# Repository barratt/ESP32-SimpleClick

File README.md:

I was looking for a simple small ESP32 that could be used as a desktop or portable IOT button.

The rationale behind not using Zigbee or BLE was simplicity & cost for the end user. It can either be connected via type C to a PC or through WiFi using a battery.

If you're looking to build one, I sent everything in the gerbers folder to JLCPCB and paid for SMD assembly. In total I paid £20 for 5 boards, so £4 per button overall. The button and LED needs soldering by hand, however since they're the biggest components, this is easy.

You can see a full bom in the gerbers folder.

Some issues that need addressing:

- The capacitors on the 3.3v line feeding the ESP are not connected. (I fixed this after using a blob of solder)
- The battery charging module does not output sufficient current with no battery connected - which means the LDO regulator does not get enough power to supply the ESP32.
This can be solved by adding 2 low drop diodes to the schematic, or just removing the battery charging and soldering the LDO input to 5v (like I did in a bodge).
- The RGB LED connector is untested - I didn't need this 
- There are no jumpers / test points to put the ESP into programming mode. As such you'll need to solder leads to the ESP directly and remove them after flashing, as shown in the images below.

It's unlikely I'll come back to the project as it solves my requirements, so if you do fix any of the above please submit a pull request, otherwise do what you like with this!

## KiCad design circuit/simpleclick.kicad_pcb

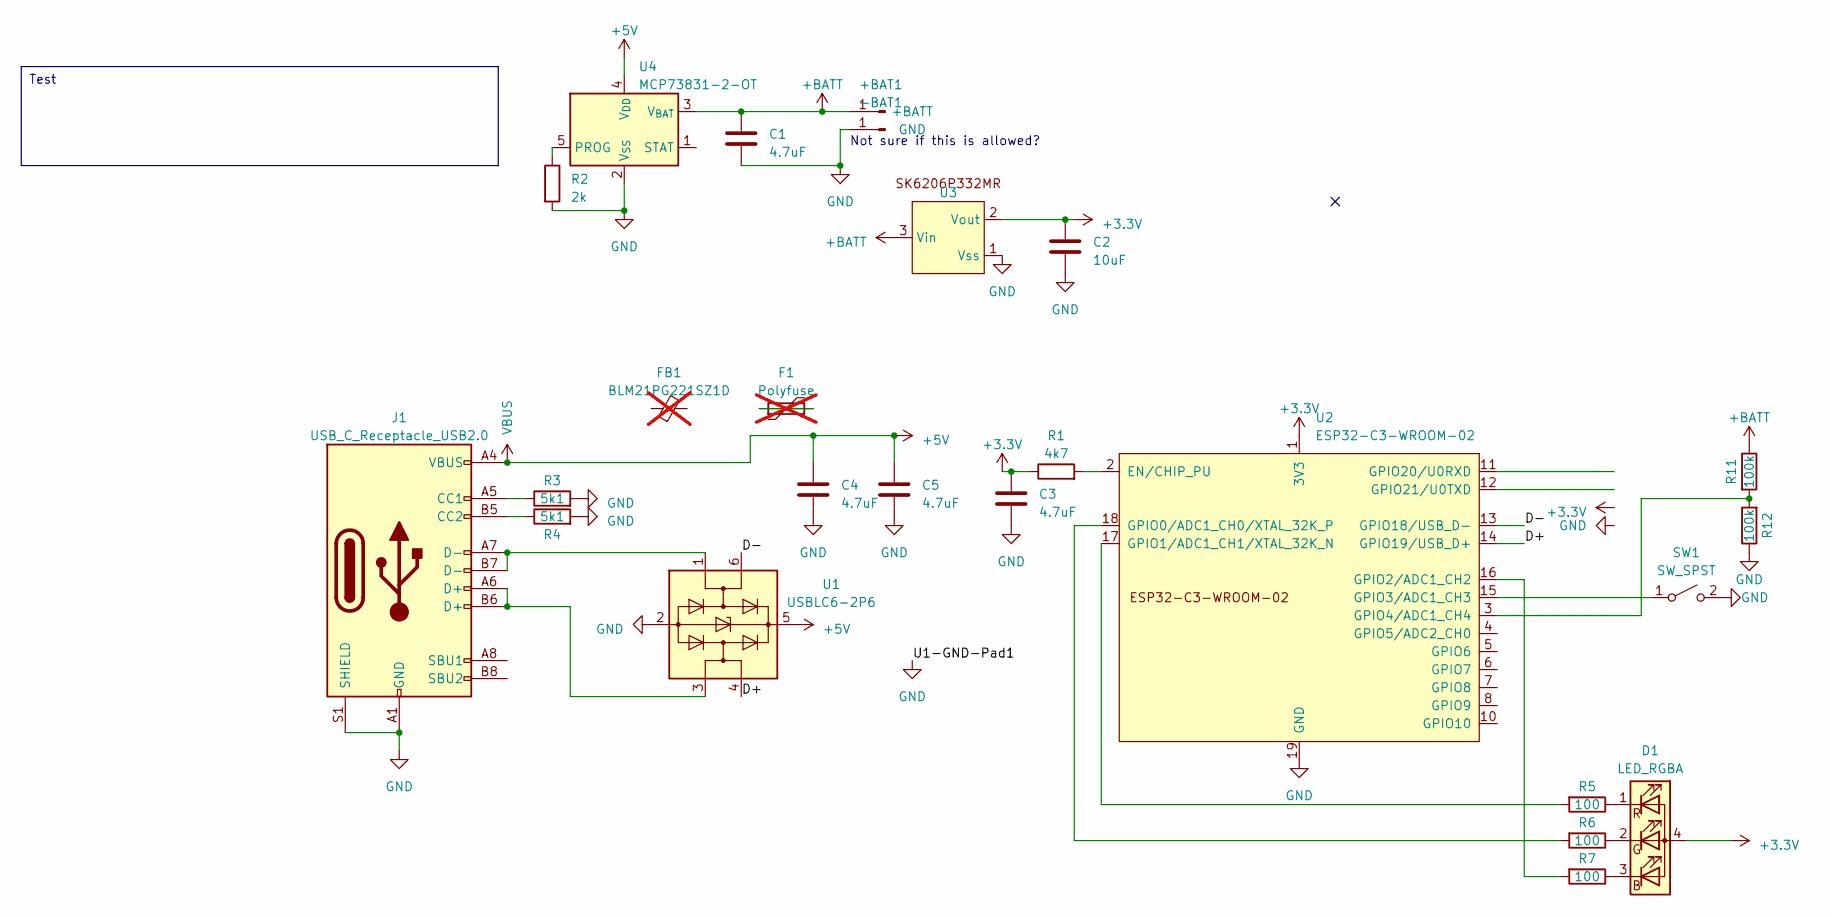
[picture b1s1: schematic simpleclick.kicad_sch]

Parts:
+BAT1: +BATT; TestPoint_Pad_D2.0mm
-BAT1: GND; TestPoint_Pad_D2.0mm
C1, C3, C4, C5: 4.7uF; C_0805_2012Metric_Pad1.18x1.45mm_HandSolder
C2: 10uF; C_0805_2012Metric_Pad1.18x1.45mm_HandSolder
D1: LED_RGBA; LED_D5.0mm-4_RGB
F1: Polyfuse; R_0805_2012Metric_Pad1.20x1.40mm_HandSolder; not fitted
FB1: BLM21PG221SZ1D; R_0805_2012Metric_Pad1.20x1.40mm_HandSolder; not fitted
J1: USB_C_Receptacle_USB2.0; USB_C_Receptacle_G-Switch_GT-USB-7010ASV
R1: 4k7; R_0805_2012Metric_Pad1.20x1.40mm_HandSolder
R2: 2k; R_0805_2012Metric_Pad1.20x1.40mm_HandSolder
R3, R4: 5k1; R_0805_2012Metric_Pad1.20x1.40mm_HandSolder
R5, R6, R7: 100; R_0603_1608Metric_Pad0.98x0.95mm_HandSolder
R11, R12: 100k; R_0805_2012Metric_Pad1.20x1.40mm_HandSolder
SW1: SW_SPST; tact12x12
U1: USBLC6-2P6; SOT-666
U2: ESP32-C3-WROOM-02
U3: SC-59_Handsoldering
U4: MCP73831-2-OT; SOT-23-5

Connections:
+3.3V: C2.1, C3.1, D1.4 (A), R1.1, U2.1 (3V3), U3.2 (Vout)
+5V: C4.1, C5.1, J1.A4 (VBUS), J1.A9 (VBUS), J1.B4 (VBUS), J1.B9 (VBUS), U1.5 (VBUS), U4.4 (V_{DD})
+BATT: +BAT1.1, C1.1, R11.1, U3.3 (Vin), U4.3 (V_{BAT})
/D+: U1.4 (I/O2), U2.14 (GPIO19/USB_D+)
/D-: U1.6 (I/O1), U2.13 (GPIO18/USB_D-)
GND: -BAT1.1, C1.2, C2.2, C3.2, C4.2, C5.2, J1.A1 (GND), J1.A12 (GND), J1.B1 (GND), J1.B12 (GND), J1.S1 (SHIELD), R2.2, R3.2, R4.2, R12.1, SW1.2 (B), U1.2 (GND), U2.9 (GND), U2.19 (GND), U3.1 (Vss), U4.2 (V_{SS})
unnamed: D1.3 (BK), R7.1
unnamed: D1.2 (GK), R6.1
unnamed: D1.1 (RK), R5.1
unnamed: F1.1, F1.2
unnamed: J1.A5 (CC1), R3.1
unnamed: J1.B5 (CC2), R4.1
unnamed: J1.A6 (D+), J1.B6 (D+), U1.3 (I/O2)
unnamed: J1.A7 (D-), J1.B7 (D-), U1.1 (I/O1)
unnamed: SW1.1 (A), U2.15 (GPIO3/ADC1_CH3)
unnamed: R1.2, U2.2 (EN/CHIP_PU)
unnamed: R6.2, U2.18 (GPIO0/ADC1_CH0/XTAL_32K_P)
unnamed: R5.2, U2.17 (GPIO1/ADC1_CH1/XTAL_32K_N)
unnamed: R7.2, U2.16 (GPIO2/ADC1_CH2)
unnamed: R11.2, R12.2, U2.3 (GPIO4/ADC1_CH4)
unnamed: R2.1, U4.5 (PROG)

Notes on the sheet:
Test
Not sure if this is allowed?

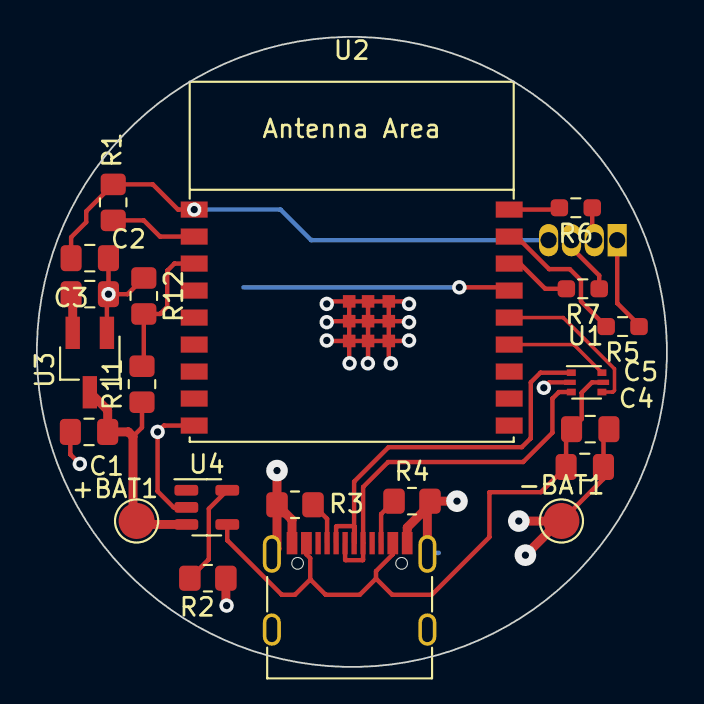
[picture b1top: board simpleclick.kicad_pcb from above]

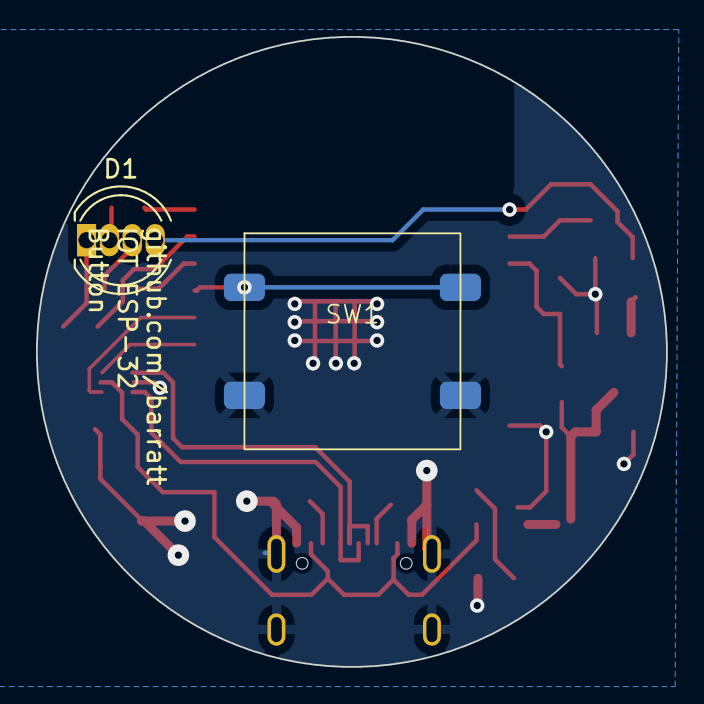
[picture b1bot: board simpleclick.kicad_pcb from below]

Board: 2 copper layers, 35.0 x 35.0 mm, 23 parts (2 on the bottom side), 20 nets.

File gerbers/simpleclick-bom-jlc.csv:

Comment,Designator,Footprint,LCSC
4u7F,"C1, C3, C4, C5",Capacitor_SMD:C_0805_2012Metric_Pad1.18x1.45mm_HandSolder,C1779
10uF,C2,Capacitor_SMD:C_0805_2012Metric_Pad1.18x1.45mm_HandSolder,C15850
BLM21PG221SZ1D,FB1,Resistor_SMD:R_0805_2012Metric_Pad1.20x1.40mm_HandSolder,C437411
SMD USB TYPE C ,J1,Connector_USB:USB_C_Receptacle_G-Switch_GT-USB-7010ASV,C2927302
4k7,R1,Resistor_SMD:R_0805_2012Metric_Pad1.20x1.40mm_HandSolder,C17673
2k,R2,Resistor_SMD:R_0805_2012Metric_Pad1.20x1.40mm_HandSolder,C17604
5k1,"R3, R4",Resistor_SMD:R_0805_2012Metric_Pad1.20x1.40mm_HandSolder,C27834
100R,"R5, R6, R7",Resistor_SMD:R_0805_2012Metric_Pad1.20x1.40mm_HandSolder,C22775
100k,"R11, R12",Resistor_SMD:R_0805_2012Metric_Pad1.20x1.40mm_HandSolder,C149504
USBLC6-2P6,U1,Package_TO_SOT_SMD:SOT-666,C2827693
ESP32-C3-WROOM-2,U2,PCM_Espressif:ESP32-C3-WROOM-02,C2934560
SK6206P332MR,U3,Package_TO_SOT_SMD:SC-59_Handsoldering,C962716
MCP73831-2-OT,U4,Package_TO_SOT_SMD:SOT-23-5,C424093
